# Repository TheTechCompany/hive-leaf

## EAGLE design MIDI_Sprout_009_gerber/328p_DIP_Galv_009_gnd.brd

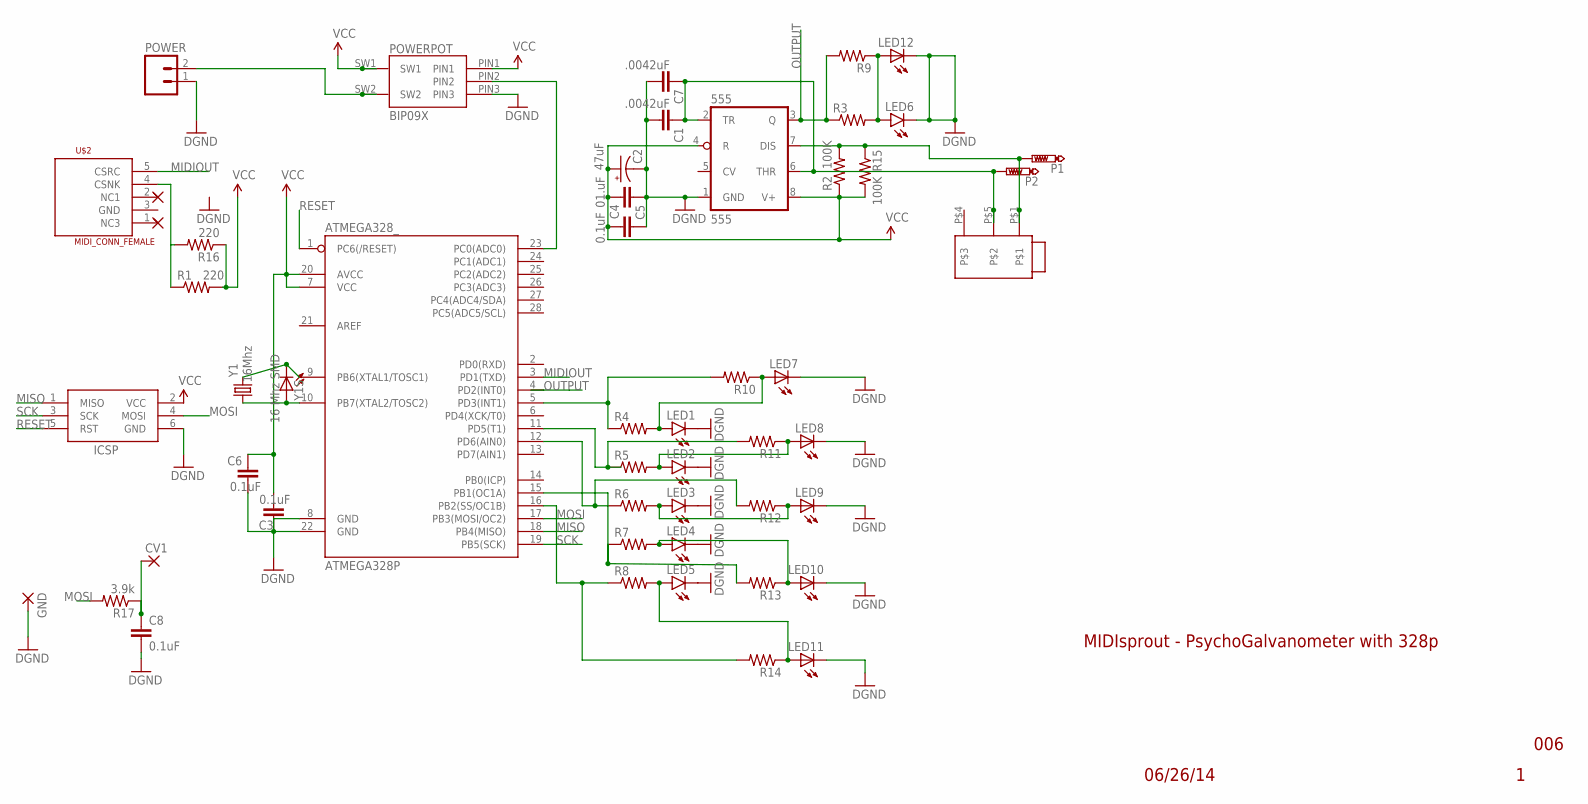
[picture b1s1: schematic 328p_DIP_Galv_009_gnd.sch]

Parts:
555: 555; DIL08-ROUND
ATMEGA328_: ATMEGA328P; DIL28-3
C1: .0042uF; CAP-PTH-SMALL
C2: 47uF; CPOL-RADIAL-10UF-25V
C3, C4: 0.1uF; CAP-PTH-SMALL
C5: 01.uF; 1206
C6, C8: 0.1uF; 1206
C7: .0042uF; 1206
CV1: 2,54/1,1
GND: 2,54/1,1
ICSP: AVRISP-6; AVRISP
LED1, LED2, LED3, LED4, LED5, LED6: LED5MM
LED7, LED8, LED9, LED10, LED11, LED12: LEDSML1206; SML1206
P1, P2: PTR1PAD1-20Y; P1-20Y
POWER: M02LOCK_LONGPADS; 1X02_LOCK_LONGPADS
POWERPOT: BIP09X
R1: 220; AXIAL-0.3
R2: 100K; AXIAL-0.3
R3, R4, R5, R6, R7, R8: RESISTORAXIAL-0.3; AXIAL-0.3
R9, R10, R11, R12, R13, R14: R-US_R1206; R1206
R15: 100K; R1206
R16: 220; R1206
R17: 3.9k; R1206
U$1: MONOJACK; MONOJACK_SWCR_3.5
U$2: MIDI_CONN_FEMALE; DIN_5_FEMALE
Y1: 16Mhz; HC49US
Y1S: 16 Mhz SMD; SML1206

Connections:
GND: 555.1 (GND), ATMEGA328_.8 (GND), ATMEGA328_.22 (GND), C1.2, C2.2 (-), C3.1, C4.2, C5.1, C6.2, C7.2, C8.2, GND.1, ICSP.6 (GND), LED1.K (C), LED2.K (C), LED3.K (C), LED4.K (C), LED5.K (C), LED6.K (C), LED7.C, LED8.C, LED9.C, LED10.C, LED11.C, LED12.C, POWER.1, POWERPOT.PIN3
MIDIOUT: ATMEGA328_.3 (PD1(TXD)), U$2.5 (CSRC)
MISO: ATMEGA328_.18 (PB4(MISO)), ICSP.1 (MISO)
MOSI: ATMEGA328_.17 (PB3(MOSI/OC2)), ICSP.4 (MOSI), R17.2
unnamed: C8.1, CV1.1, R17.1
unnamed: ATMEGA328_.10 (PB7(XTAL2/TOSC2)), Y1.1, Y1S.A
unnamed: ATMEGA328_.9 (PB6(XTAL1/TOSC1)), Y1.2, Y1S.C
unnamed: ATMEGA328_.23 (PC0(ADC0)), POWERPOT.PIN2
unnamed: R1.P$1 (1), R16.2, U$2.4 (CSNK)
unnamed: ATMEGA328_.5 (PD3(INT1)), R4.P$1 (1), R10.2
unnamed: ATMEGA328_.11 (PD5(T1)), R5.P$1 (1), R11.2
unnamed: ATMEGA328_.12 (PD6(AIN0)), R6.P$1 (1), R12.2
unnamed: POWER.2, POWERPOT.SW2
unnamed: ATMEGA328_.15 (PB1(OC1A)), R7.P$1 (1), R13.2
unnamed: ATMEGA328_.16 (PB2(SS/OC1B)), R8.P$1 (1), R14.2
unnamed: LED1.A, LED7.A, R4.P$2 (2), R10.1
unnamed: LED2.A, LED8.A, R5.P$2 (2), R11.1
unnamed: LED3.A, LED9.A, R6.P$2 (2), R12.1
unnamed: LED4.A, LED10.A, R7.P$2 (2), R13.1
unnamed: LED5.A, LED11.A, R8.P$2 (2), R14.1
unnamed: LED6.A, LED12.A, R3.P$2 (2), R9.1
OUTPUT: 555.3 (Q), ATMEGA328_.4 (PD2(INT0)), R3.P$1 (1), R9.2
PROBE1: 555.2 (TR), 555.6 (THR), C1.1, C7.1, P2.TP, U$1.P$5
PROBE2: 555.7 (DIS), P1.TP, R2.P$2 (2), R15.1, U$1.P$1
RESET: ATMEGA328_.1 (PC6(/RESET)), ICSP.5 (RST)
SCK: ATMEGA328_.19 (PB5(SCK)), ICSP.3 (SCK)
VCC: 555.4 (R), 555.8 (V+), ATMEGA328_.7 (VCC), ATMEGA328_.20 (AVCC), C2.1 (+), C3.2, C4.1, C5.2, C6.1, ICSP.2 (VCC), POWERPOT.PIN1, POWERPOT.SW1, R1.P$2 (2), R2.P$1 (1), R15.2, R16.1

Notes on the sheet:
06/26/14
006
MIDIsprout - PsychoGalvanometer with 328p

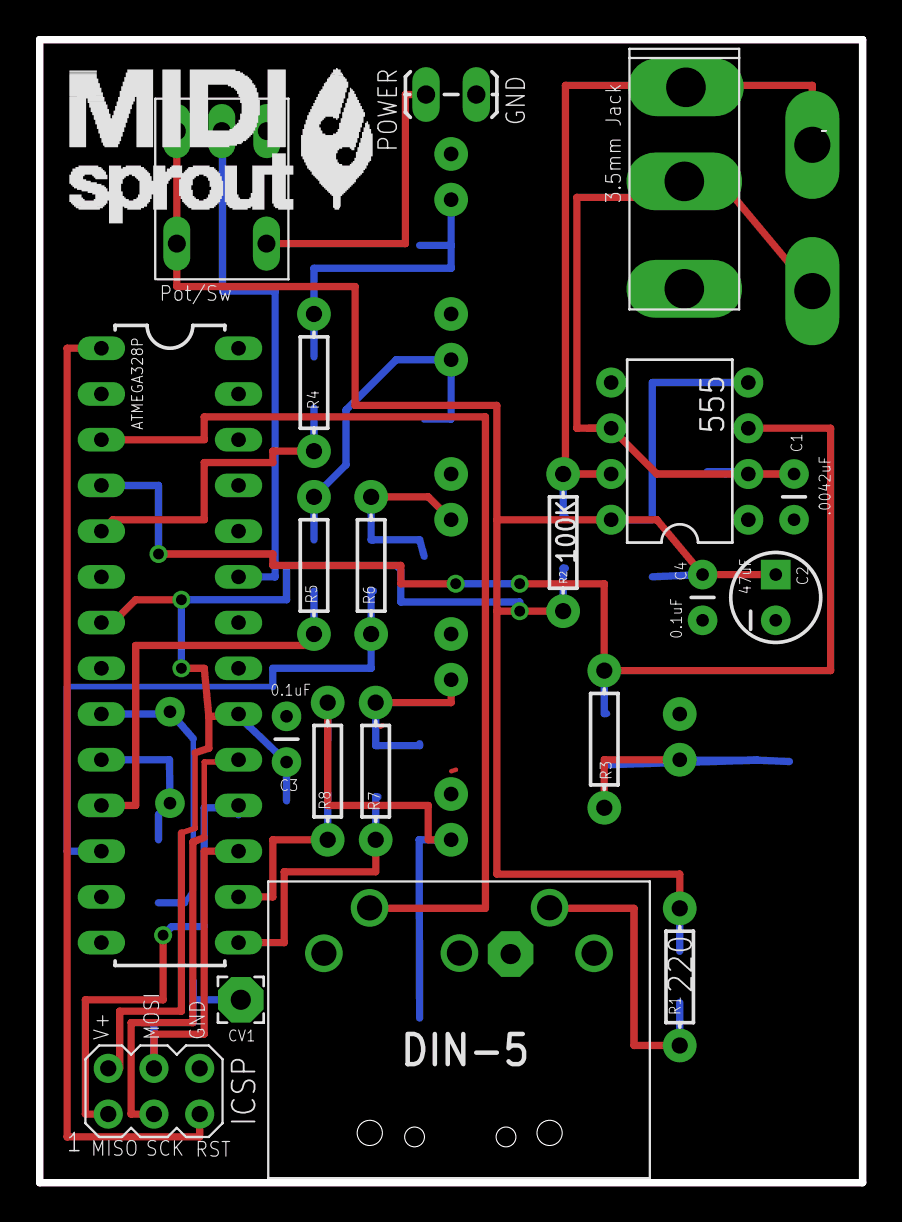
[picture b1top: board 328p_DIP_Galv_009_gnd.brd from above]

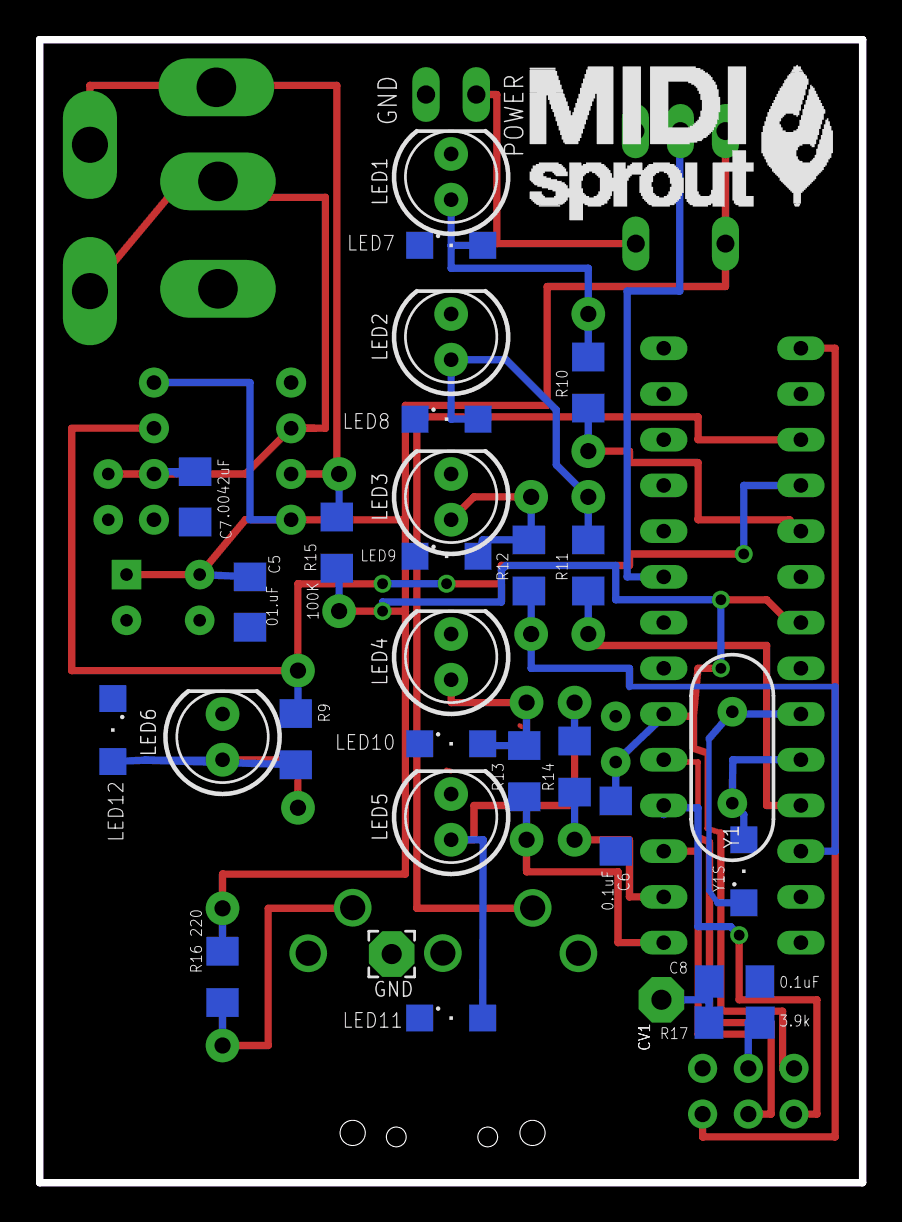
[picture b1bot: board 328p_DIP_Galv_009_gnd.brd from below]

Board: 2 copper layers, 45.7 x 63.5 mm, 50 parts (28 on the bottom side), 27 nets.

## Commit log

2021-06-30 init

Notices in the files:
parts and their libraries:
SparkFun-Connectors: Licensing: Creative Commons ShareAlike 4.0 International - https://creativecommons.org/licenses/by-sa/4.0
